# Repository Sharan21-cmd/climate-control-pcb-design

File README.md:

🌡️ Climate Control System – PCB Design

A compact and efficient Climate Control PCB designed for monitoring and regulating temperature and humidity using embedded electronics.
This board integrates multiple sensors, a microcontroller, power regulation circuitry, and output drivers to control cooling/heating units.

🚀 Project Overview

This project focuses on building a complete hardware solution for climate control applications such as:

Greenhouse automation
Home/room temperature control
Industrial environment monitoring
Smart HVAC systems

The PCB is designed using KiCad 6/7/8/9 and follows proper routing, grounding, and noise-reduction guidelines.

🔧 Features
Sensing
🌡️ Temperature Sensor (e.g., DHT22, NTC, or DS18B20)
💧 Humidity Measurement
Real-time environment monitoring
Control
🔥 Heating element control (Relay / MOSFET)
❄️ Cooling fan/motor output
⚡ PWM-based fan speed control
Microcontroller
ESP8266 / ESP32 / STM32 / Arduino-compatible MCU
Supports WiFi (optional)
GPIO protection and filter network
Power
5V → 3.3V LDO/AMS1117 regulator
Reverse polarity protection
Fuse protection
Decoupling capacitors placed near IC pins
🖼️ Project Files

This repository contains:

/project_name.kicad_pro  
/project_name.kicad_sch  
/project_name.kicad_pcb  
/gerber/  
/bom/  
/readme.md  
🧩 PCB Highlights
2-layer compact PCB
Ground plane for noise reduction
Thick traces for relay/fan output
Sensor signals routed with noise isolation
Proper silkscreen labeling
Edge-cuts fully validated with DRC

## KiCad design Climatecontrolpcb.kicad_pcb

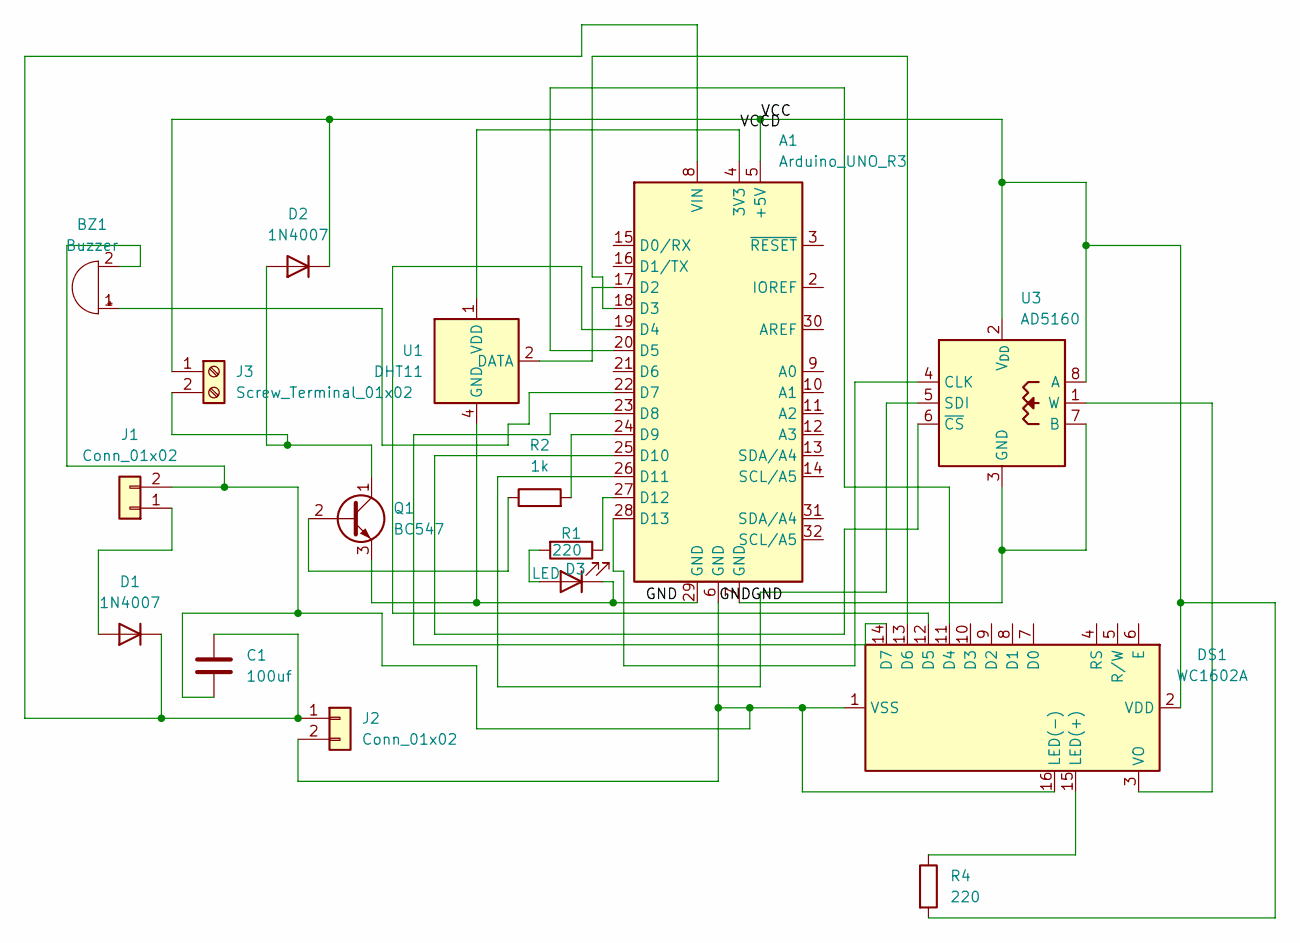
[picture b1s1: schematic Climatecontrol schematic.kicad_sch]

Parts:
A1: Arduino_UNO_R3
BZ1: Buzzer; Buzzer_12x9.5RM7.6
C1: 100uf; C_Disc_D5.0mm_W2.5mm_P2.50mm
D1, D2: 1N4007; D_DO-41_SOD81_P10.16mm_Horizontal
D3: LED; LED_0201_0603Metric
DS1: WC1602A
J1: Conn_01x02; PhoenixContact_MSTBA_2,5_2-G-5,08_1x02_P5.08mm_Horizontal
J2: Conn_01x02; PinHeader_1x02_P2.54mm_Vertical
J3: Screw_Terminal_01x02; TerminalBlock_MaiXu_MX126-5.0-02P_1x02_P5.00mm
Q1: BC547; TO-92_Inline
R1: 220; R_0201_0603Metric_Pad0.64x0.40mm_HandSolder
R2: 1k; R_0201_0603Metric_Pad0.64x0.40mm_HandSolder
R4: 220; R_0402_1005Metric_Pad0.72x0.64mm_HandSolder
U1: DHT11; Aosong_DHT11_5.5x12.0_P2.54mm
U3: AD5160; SOT-23-8

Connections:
/GND: A1.6 (GND), A1.7 (GND), A1.29 (GND), BZ1.2 (-), C1.2, D3.1 (K), DS1.1 (VSS), DS1.16 (LED(-)), J1.2, J2.2, Q1.3 (E), U1.4 (GND), U3.3 (GND), U3.7 (B)
/VCC: A1.5 (+5V), D2.1 (K), DS1.2 (VDD), J3.1, R4.2, U3.2 (V_{DD}), U3.8 (A)
/VCCD: A1.4 (3V3), U1.1 (VDD)
unnamed: A1.17 (D2), U1.2 (DATA)
unnamed: A1.18 (D3), DS1.13 (D6)
unnamed: A1.19 (D4), DS1.12 (D5)
unnamed: A1.20 (D5), DS1.11 (D4)
unnamed: A1.22 (D7), BZ1.1 (+)
unnamed: A1.23 (D8), DS1.14 (D7)
unnamed: A1.24 (D9), R2.2
unnamed: A1.25 (D10), U3.6 (~CS)
unnamed: A1.26 (D11), U3.5 (SDI)
unnamed: A1.27 (D12), R1.1
unnamed: A1.28 (D13), U3.4 (CLK)
unnamed: A1.8 (VIN), C1.1, D1.1 (K), J2.1
unnamed: D1.2 (A), J1.1
unnamed: D2.2 (A), J3.2, Q1.1 (C)
unnamed: D3.2 (A), R1.2
unnamed: DS1.15 (LED(+)), R4.1
unnamed: DS1.3 (VO), U3.1 (W)
unnamed: Q1.2 (B), R2.1

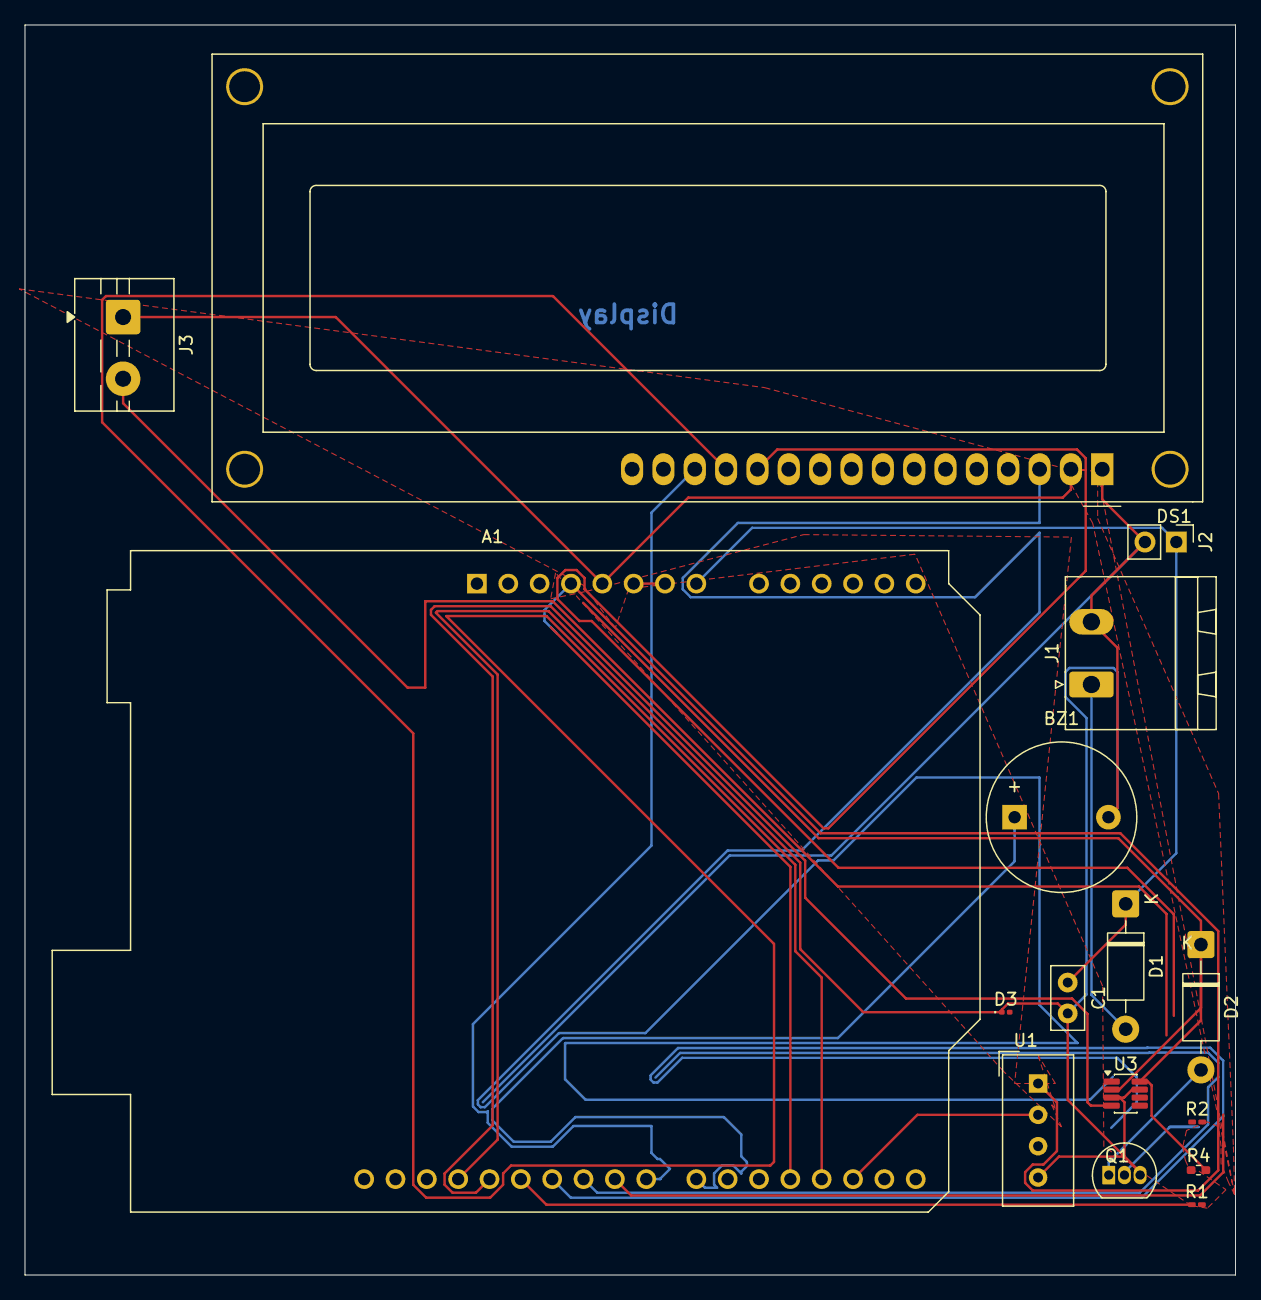
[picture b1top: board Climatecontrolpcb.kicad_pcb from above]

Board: 2 copper layers, 98.1 x 101.3 mm, 16 parts (0 on the bottom side), 21 nets.
